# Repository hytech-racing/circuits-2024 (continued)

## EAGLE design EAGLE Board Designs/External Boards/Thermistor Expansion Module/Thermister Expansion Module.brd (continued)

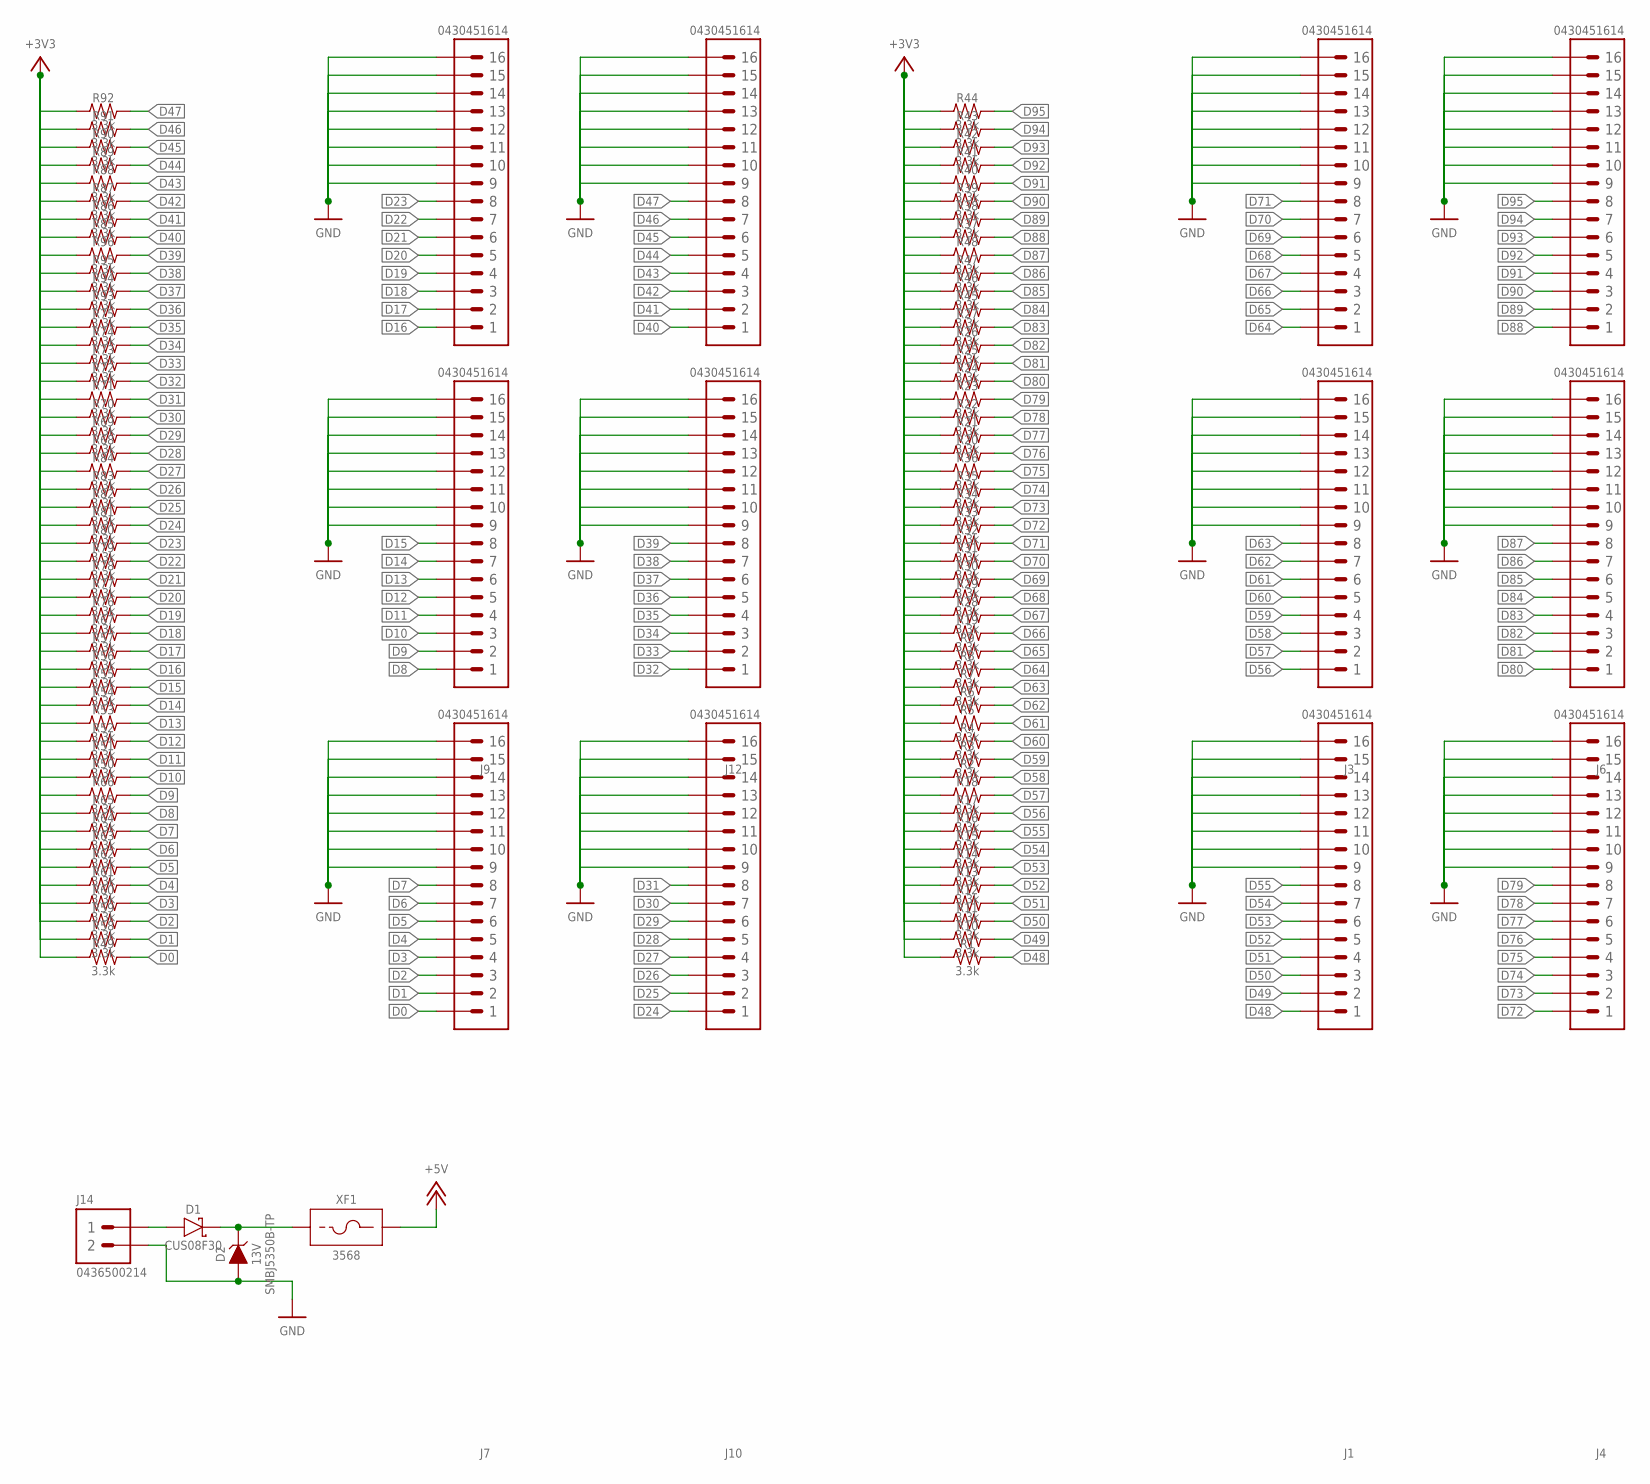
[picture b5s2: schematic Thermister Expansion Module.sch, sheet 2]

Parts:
D1: SCHOTTKY_SOD323_30V; SOD-323
D2: ZENER_SMB(DO-214AA)_13V; SMB(DO-214AA)
J1, J2, J3, J4, J5, J6, J7, J8, J9, J10, J11, J12: CONNECTOR-16_MF_T_V_; MOLEX_MICROFIT_PTH_VERTICAL_16_DUAL
J14: CONNECTOR-2_MICROFIT_SMD_RIGHTANGLE_02_SINGLE_BLA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; MOLEX_MICROFIT_SMD_RIGHTANGLE_02_SINGLE
R1, R2, R3, R4, R5, R6, R7, R8, R9, R10, R11, R12, R13, R14, R15, R16, R17, R18, R19, R20, R21, R22, R23, R24, R25, R26, R27, R28, R29, R30, R31, R32, R33, R34, R35, R36, R37, R38, R39, R40, R41, R42, R43, R44, R45, R46, R47, R48, R49, R50, R51, R52, R53, R54, R55, R56, R57, R58, R59, R60, R61, R62, R63, R64, R65, R66, R67, R68, R69, R70, R71, R72, R73, R74, R75, R76, R77, R78, R79, R80, R81, R82, R83, R84, R85, R86, R87, R88, R89, R90, R91, R92, R93, R94, R95, R96: RESISTOR_0603_3.3K; 0603-RES
XF1: FUSE_HOLDER_MINIBLADEPTH; 3568

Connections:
+3V3: R1.1, R2.1, R3.1, R4.1, R5.1, R6.1, R7.1, R8.1, R9.1, R10.1, R11.1, R12.1, R13.1, R14.1, R15.1, R16.1, R17.1, R18.1, R19.1, R20.1, R21.1, R22.1, R23.1, R24.1, R25.1, R26.1, R27.1, R28.1, R29.1, R30.1, R31.1, R32.1, R33.1, R34.1, R35.1, R36.1, R37.1, R38.1, R39.1, R40.1, R41.1, R42.1, R43.1, R44.1, R45.1, R46.1, R47.1, R48.1, R49.1, R50.1, R51.1, R52.1, R53.1, R54.1, R55.1, R56.1, R57.1, R58.1, R59.1, R60.1, R61.1, R62.1, R63.1, R64.1, R65.1, R66.1, R67.1, R68.1, R69.1, R70.1, R71.1, R72.1, R73.1, R74.1, R75.1, R76.1, R77.1, R78.1, R79.1, R80.1, R81.1, R82.1, R83.1, R84.1, R85.1, R86.1, R87.1, R88.1, R89.1, R90.1, R91.1, R92.1, R93.1, R94.1, R95.1, R96.1; also elsewhere on the board
+5V: XF1.3 (2), XF1.4 (2); also elsewhere on the board
D0: J7.1, R49.2; also elsewhere on the board
D1: J7.2, R58.2; also elsewhere on the board
D2: J7.3, R59.2; also elsewhere on the board
D3: J7.4, R60.2; also elsewhere on the board
D4: J7.5, R61.2; also elsewhere on the board
D5: J7.6, R62.2; also elsewhere on the board
D6: J7.7, R63.2; also elsewhere on the board
D7: J7.8, R64.2; also elsewhere on the board
D8: J8.1, R65.2; also elsewhere on the board
D9: J8.2, R66.2; also elsewhere on the board
D10: J8.3, R50.2; also elsewhere on the board
D11: J8.4, R51.2; also elsewhere on the board
D12: J8.5, R52.2; also elsewhere on the board
D13: J8.6, R53.2; also elsewhere on the board
D14: J8.7, R54.2; also elsewhere on the board
D15: J8.8, R55.2; also elsewhere on the board
D16: J9.1, R56.2; also elsewhere on the board
D17: J9.2, R57.2; also elsewhere on the board
D18: J9.3, R67.2; also elsewhere on the board
D19: J9.4, R76.2; also elsewhere on the board
D20: J9.5, R77.2; also elsewhere on the board
D21: J9.6, R78.2; also elsewhere on the board
D22: J9.7, R79.2; also elsewhere on the board
D23: J9.8, R80.2; also elsewhere on the board
D24: J10.1, R81.2; also elsewhere on the board
D25: J10.2, R82.2; also elsewhere on the board
D26: J10.3, R83.2; also elsewhere on the board
D27: J10.4, R84.2; also elsewhere on the board
D28: J10.5, R68.2; also elsewhere on the board
D29: J10.6, R69.2; also elsewhere on the board
D30: J10.7, R70.2; also elsewhere on the board
D31: J10.8, R71.2; also elsewhere on the board
D32: J11.1, R72.2; also elsewhere on the board
D33: J11.2, R73.2; also elsewhere on the board
D34: J11.3, R74.2; also elsewhere on the board
D35: J11.4, R75.2; also elsewhere on the board
D36: J11.5, R93.2; also elsewhere on the board
D37: J11.6, R94.2; also elsewhere on the board
D38: J11.7, R95.2; also elsewhere on the board
D39: J11.8, R96.2; also elsewhere on the board
D40: J12.1, R85.2; also elsewhere on the board
D41: J12.2, R86.2; also elsewhere on the board
D42: J12.3, R87.2; also elsewhere on the board
D43: J12.4, R88.2; also elsewhere on the board
D44: J12.5, R89.2; also elsewhere on the board
D45: J12.6, R90.2; also elsewhere on the board
D46: J12.7, R91.2; also elsewhere on the board
D47: J12.8, R92.2; also elsewhere on the board
D48: J1.1, R1.2; also elsewhere on the board
D49: J1.2, R10.2; also elsewhere on the board
D50: J1.3, R11.2; also elsewhere on the board
D51: J1.4, R12.2; also elsewhere on the board
D52: J1.5, R13.2; also elsewhere on the board
D53: J1.6, R14.2; also elsewhere on the board
D54: J1.7, R15.2; also elsewhere on the board
D55: J1.8, R16.2; also elsewhere on the board
D56: J2.1, R17.2; also elsewhere on the board
D57: J2.2, R18.2; also elsewhere on the board
D58: J2.3, R2.2; also elsewhere on the board
D59: J2.4, R3.2; also elsewhere on the board
D60: J2.5, R4.2; also elsewhere on the board
D61: J2.6, R5.2; also elsewhere on the board
D62: J2.7, R6.2; also elsewhere on the board
D63: J2.8, R7.2; also elsewhere on the board
D64: J3.1, R8.2; also elsewhere on the board
D65: J3.2, R9.2; also elsewhere on the board
D66: J3.3, R19.2; also elsewhere on the board
D67: J3.4, R28.2; also elsewhere on the board
D68: J3.5, R29.2; also elsewhere on the board
D69: J3.6, R30.2; also elsewhere on the board
D70: J3.7, R31.2; also elsewhere on the board
D71: J3.8, R32.2; also elsewhere on the board
D72: J4.1, R33.2; also elsewhere on the board
D73: J4.2, R34.2; also elsewhere on the board
D74: J4.3, R35.2; also elsewhere on the board
D75: J4.4, R36.2; also elsewhere on the board
D76: J4.5, R20.2; also elsewhere on the board
D77: J4.6, R21.2; also elsewhere on the board
D78: J4.7, R22.2; also elsewhere on the board
D79: J4.8, R23.2; also elsewhere on the board
D80: J5.1, R24.2; also elsewhere on the board
D81: J5.2, R25.2; also elsewhere on the board
D82: J5.3, R26.2; also elsewhere on the board
D83: J5.4, R27.2; also elsewhere on the board
D84: J5.5, R45.2; also elsewhere on the board
D85: J5.6, R46.2; also elsewhere on the board
D86: J5.7, R47.2; also elsewhere on the board
D87: J5.8, R48.2; also elsewhere on the board
D88: J6.1, R37.2; also elsewhere on the board
D89: J6.2, R38.2; also elsewhere on the board
D90: J6.3, R39.2; also elsewhere on the board
D91: J6.4, R40.2; also elsewhere on the board
D92: J6.5, R41.2; also elsewhere on the board
D93: J6.6, R42.2; also elsewhere on the board
D94: J6.7, R43.2; also elsewhere on the board
D95: J6.8, R44.2; also elsewhere on the board
GND: D2.A, J1.9, J1.10, J1.11, J1.12, J1.13, J1.14, J1.15, J1.16, J2.9, J2.10, J2.11, J2.12, J2.13, J2.14, J2.15, J2.16, J3.9, J3.10, J3.11, J3.12, J3.13, J3.14, J3.15, J3.16, J4.9, J4.10, J4.11, J4.12, J4.13, J4.14, J4.15, J4.16, J5.9, J5.10, J5.11, J5.12, J5.13, J5.14, J5.15, J5.16, J6.9, J6.10, J6.11, J6.12, J6.13, J6.14, J6.15, J6.16, J7.9, J7.10, J7.11, J7.12, J7.13, J7.14, J7.15, J7.16, J8.9, J8.10, J8.11, J8.12, J8.13, J8.14, J8.15, J8.16, J9.9, J9.10, J9.11, J9.12, J9.13, J9.14, J9.15, J9.16, J10.9, J10.10, J10.11, J10.12, J10.13, J10.14, J10.15, J10.16, J11.9, J11.10, J11.11, J11.12, J11.13, J11.14, J11.15, J11.16, J12.9, J12.10, J12.11, J12.12, J12.13, J12.14, J12.15, J12.16, J14.2; also elsewhere on the board
unnamed: D1.A, J14.1
unnamed: D1.C, D2.C, XF1.1, XF1.2 (1)

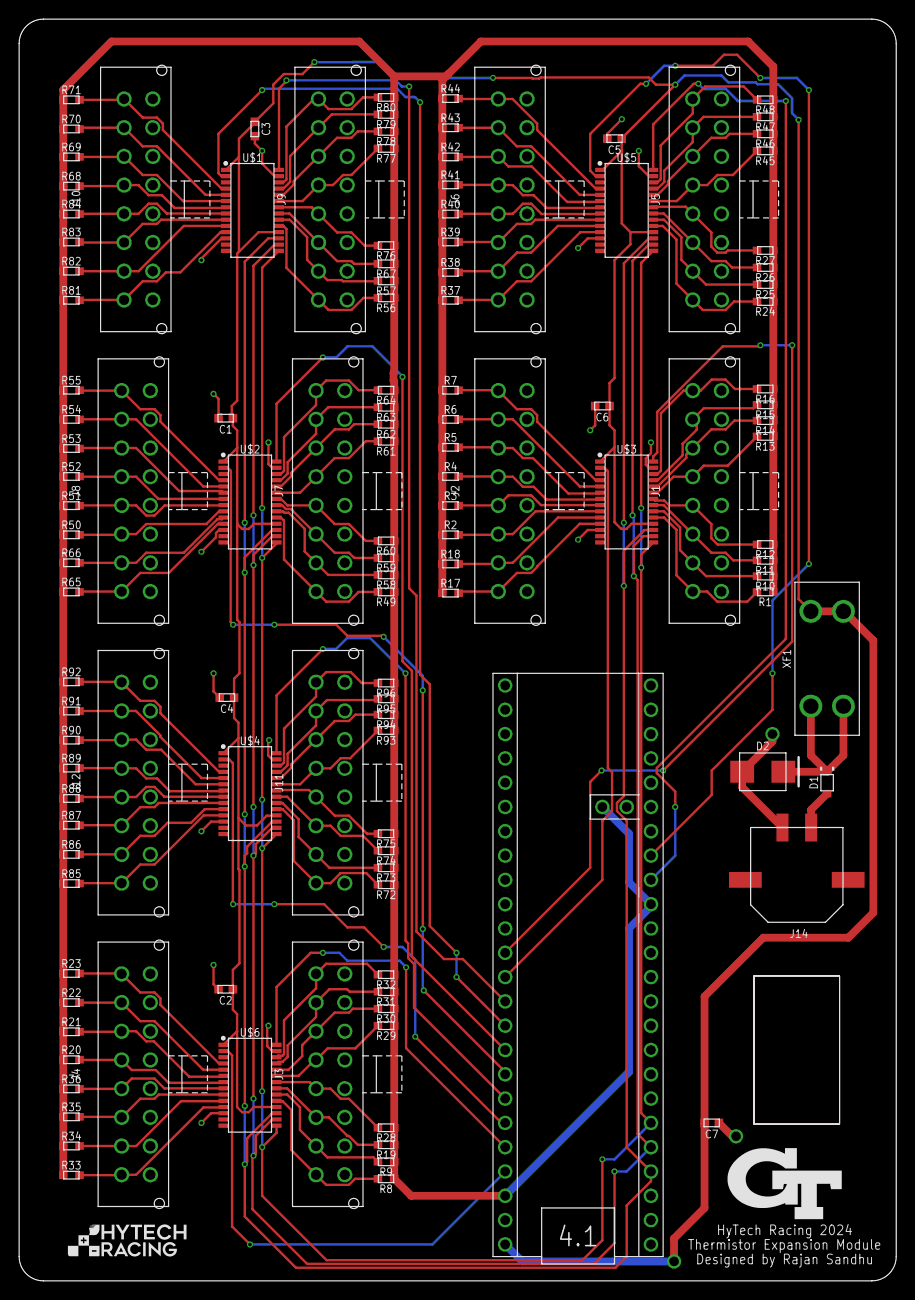
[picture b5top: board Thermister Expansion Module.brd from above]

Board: 2 copper layers, 91.7 x 131.9 mm, 128 parts (0 on the bottom side), 116 nets.

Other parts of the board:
U$7: LOGO_GT_MEDIUM
U$8: LOGO_HYTECH_SMALL

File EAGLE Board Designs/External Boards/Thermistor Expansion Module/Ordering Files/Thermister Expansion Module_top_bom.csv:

Comment,Designator,Footprint,LCSC Part #
ADG707,U$1 U$2 U$3 U$4 U$5 U$6,TSSOP-28,
CAPACITOR_0603_10V_1UF,C1 C2 C3 C4 C5 C6 C7,0603-CAP,
CONNECTOR-2_MICROFIT_SMD_RIGHTANGLE_02_SINGLE_BLACK,J14,MOLEX_MICROFIT_SMD_RIGHTANGLE_02_SINGLE,
RESISTOR_0603_3.3K,R1 R2 R3 R4 R5 R6 R7 R8 R9 R10 R11 R12 R13 R14 R15 R16 R17 R18 R19 R20 R21 R22 R23 R24 R25 R26 R27 R28 R29 R30 R31 R32 R33 R34 R35 R36 R37 R38 R39 R40 R41 R42 R43 R44 R45 R46 R47 R48 R49 R50 R51 R52 R53 R54 R55 R56 R57 R58 R59 R60 R61 R62 R63 R64 R65 R66 R67 R68 R69 R70 R71 R72 R73 R74 R75 R76 R77 R78 R79 R80 R81 R82 R83 R84 R85 R86 R87 R88 R89 R90 R91 R92 R93 R94 R95 R96,0603-RES,
SCHOTTKY_SOD323_30V,D1,SOD-323,
ZENER_SMB(DO-214AA)_13V,D2,SMB(DO-214AA),
